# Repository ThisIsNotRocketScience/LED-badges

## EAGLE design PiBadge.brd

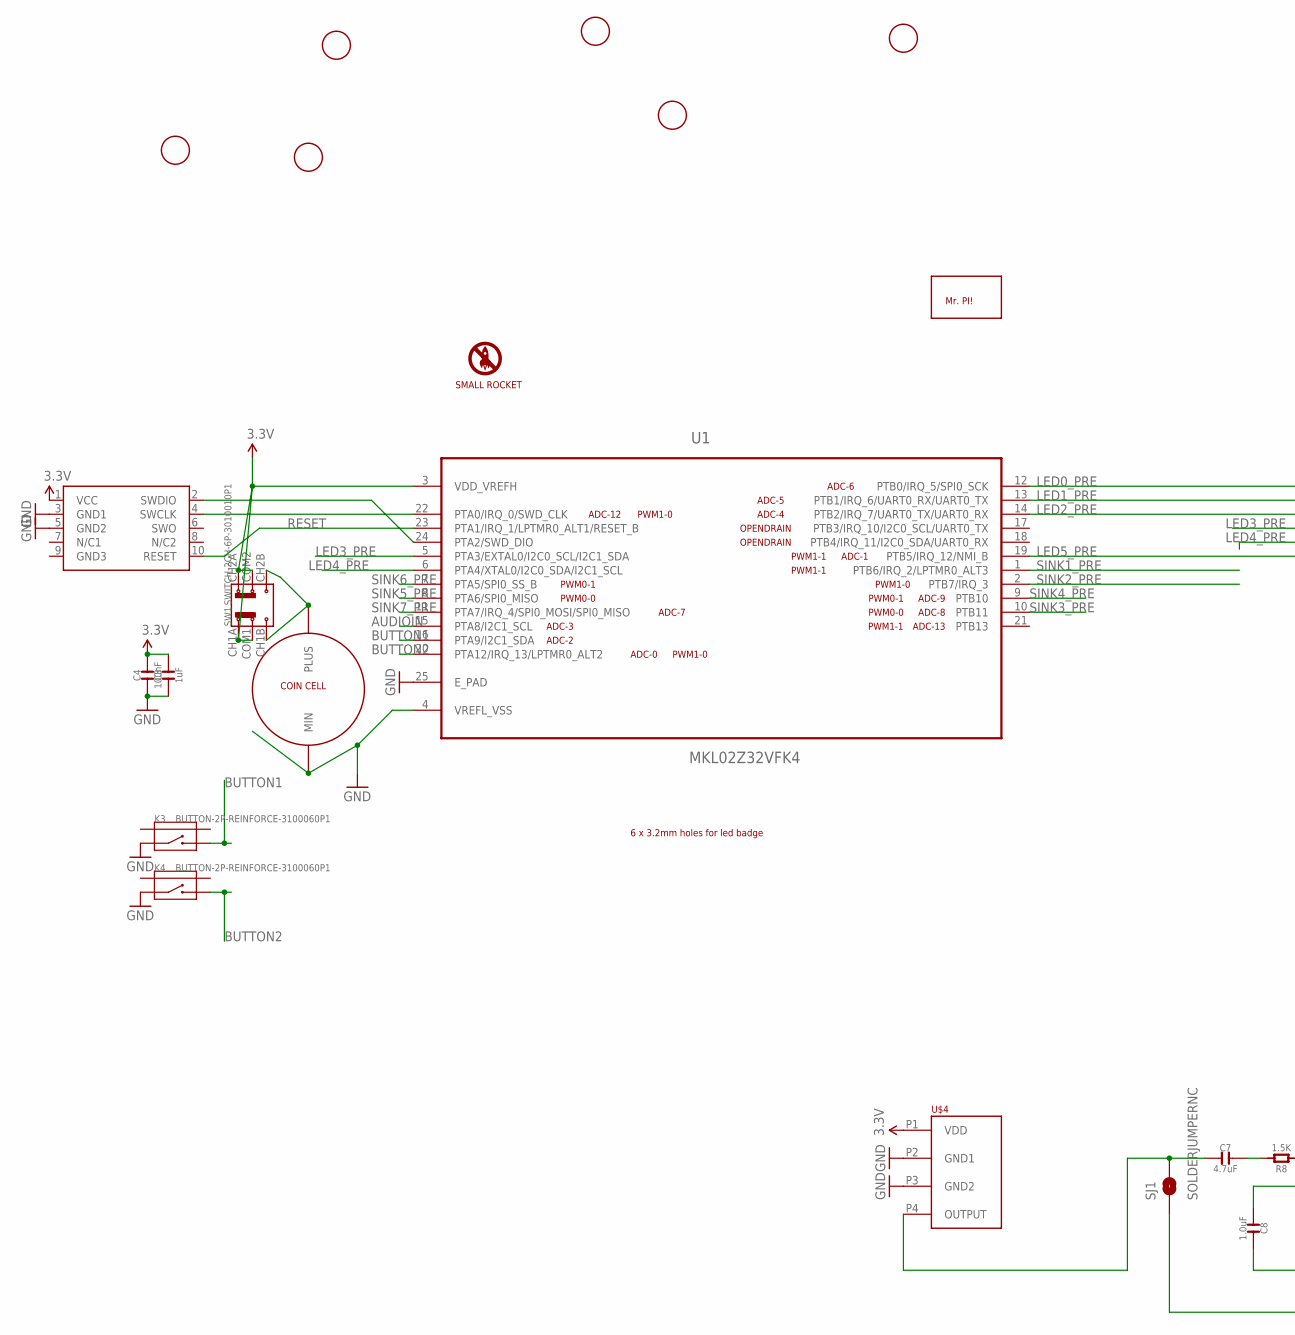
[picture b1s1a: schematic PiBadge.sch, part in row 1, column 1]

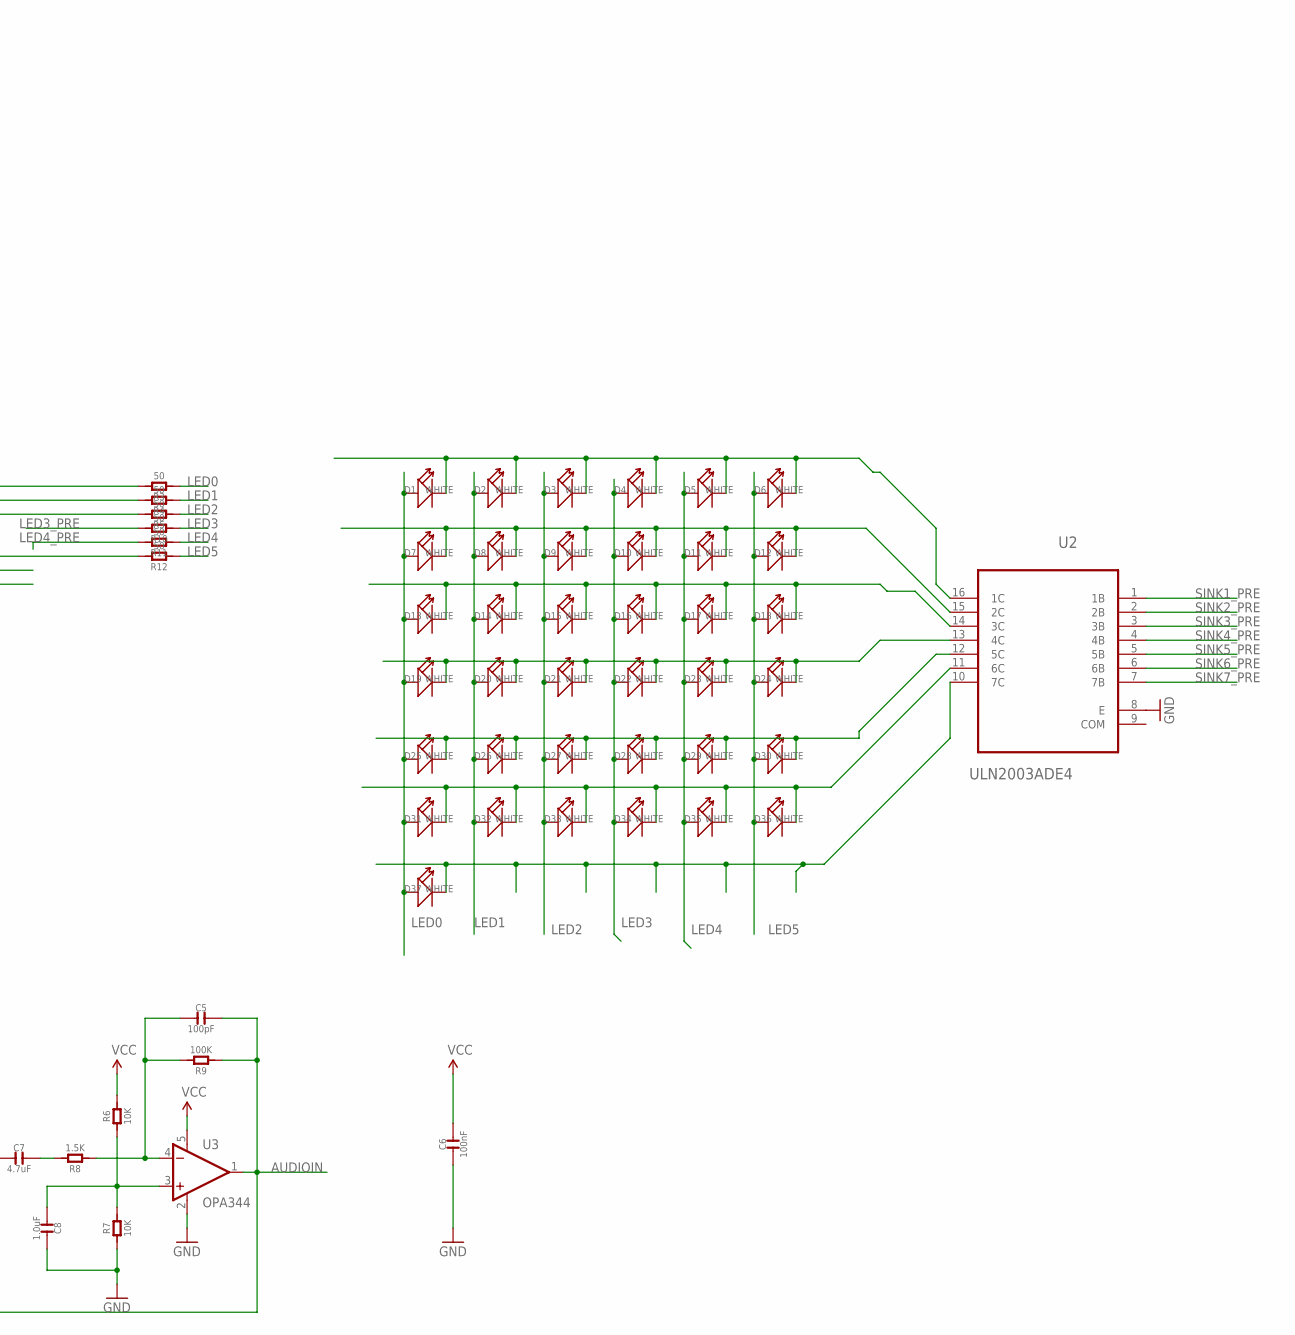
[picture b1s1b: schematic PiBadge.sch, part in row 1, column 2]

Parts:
C3: 1uF; C0603
C4, C6: 100nF; C0603
C5: 100pF; C0603
C7: 4.7uF; C0603
C8: 1.0uF; C0603
D1, D2, D3, D4, D5, D6, D7, D8, D9, D10, D11, D12, D13, D14, D15, D16, D17, D18, D19, D20, D21, D22, D23, D24, D25, D26, D27, D28, D29, D30, D31, D32, D33, D34, D35, D36, D37: WHITE; LED0805
K3, K4: BUTTON-2P-REINFORCE-3100060P1; 4P-SMD-7.0X3.5X3.5H-90D
R3, R4, R5, R10, R11, R12: 50; R0603
R6, R7: 10K; R0603
R8: 1.5K; R0603
R9: 100K; R0603
SJ1: SOLDERJUMPERNC; SJ_2S
SW1: SWITCH-2CH-6P-3010010P1; 6P-2CH-2.54-9.1X3.5X3.2+2H
SWD1: CORTEX_SWD; M50-3600542
U1: MKL02Z32VFK4; QFN50P400X400X100-25N
U2: ULN2003ADE4; SOIC127P600X175-16N
U3: OPA344; SOT23-5
U$1: SMALLROCKET
U$2: COINCELL; 2032HOLDER-SZ
U$3, U$6, U$7, U$8, U$9, U$10: FIDUCIAL; FIDUCIAL_1MM
U$4: WM7120A; LGAMS4
U$5: BADGE_HOLES; BADGEHOLES
U$11: PITINY; TINYPI

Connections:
3.3V: C3.2, C4.2, C6.2, R6.2, SW1.CH1A, SW1.CH2A, SW1.COM1, SW1.COM2, SWD1.1 (VCC), U1.3 (VDD_VREFH), U3.5 (V+), U$4.P1 (VDD)
AUDIOIN: C5.2, R9.1, SJ1.1, U1.15 (PTA8/I2C1_SCL), U3.1 (OUT)
BUTTON1: K3.2, U1.16 (PTA9/I2C1_SDA)
BUTTON2: K4.2, U1.20 (PTA12/IRQ_13/LPTMR0_ALT2)
GND: C3.1, C4.1, C6.1, C8.2, K3.1, K4.1, R7.1, SWD1.3 (GND1), SWD1.5 (GND2), U1.4 (VREFL_VSS), U1.25 (E_PAD), U2.8 (E), U3.2 (V-), U$2.MIN, U$4.P2 (GND1), U$4.P3 (GND2)
LED0: D1.+, D7.+, D13.+, D19.+, D25.+, D31.+, D37.+, R3.1
LED0_PRE: R3.2, U1.12 (PTB0/IRQ_5/SPI0_SCK)
LED1: D2.+, D8.+, D14.+, D20.+, D26.+, D32.+, R4.1
LED1_PRE: R4.2, U1.13 (PTB1/IRQ_6/UART0_RX/UART0_TX)
LED2: D3.+, D9.+, D15.+, D21.+, D27.+, D33.+, R5.1
LED2_PRE: R5.2, U1.14 (PTB2/IRQ_7/UART0_TX/UART0_RX)
LED3: D4.+, D10.+, D16.+, D22.+, D28.+, D34.+, R10.1
LED3_PRE: R10.2, U1.5 (PTA3/EXTAL0/I2C0_SCL/I2C1_SDA)
LED4: D5.+, D11.+, D17.+, D23.+, D29.+, D35.+, R11.1
LED4_PRE: R11.2, U1.6 (PTA4/XTAL0/I2C0_SDA/I2C1_SCL)
LED5: D6.+, D12.+, D18.+, D24.+, D30.+, D36.+, R12.1
LED5_PRE: R12.2, U1.19 (PTB5/IRQ_12/NMI_B)
unnamed: SW1.CH1B, SW1.CH2B, U$2.PLUS
unnamed: SWD1.4 (SWCLK), U1.22 (PTA0/IRQ_0/SWD_CLK)
unnamed: SWD1.2 (SWDIO), U1.24 (PTA2/SWD_DIO)
unnamed: C7.1, SJ1.2, U$4.P4 (OUTPUT)
unnamed: C5.1, R8.1, R9.2, U3.4 (-IN)
unnamed: C7.2, R8.2
unnamed: C8.1, R6.1, R7.2, U3.3 (+IN)
RESET: SWD1.10 (RESET), U1.23 (PTA1/IRQ_1/LPTMR0_ALT1/RESET_B)
SINK1: D1.-, D2.-, D3.-, D4.-, D5.-, D6.-, U2.16 (1C)
SINK1_PRE: U1.1 (PTB6/IRQ_2/LPTMR0_ALT3), U2.1 (1B)
SINK2: D7.-, D8.-, D9.-, D10.-, D11.-, D12.-, U2.15 (2C)
SINK2_PRE: U1.2 (PTB7/IRQ_3), U2.2 (2B)
SINK3: D13.-, D14.-, D15.-, D16.-, D17.-, D18.-, U2.14 (3C)
SINK3_PRE: U1.10 (PTB11), U2.3 (3B)
SINK4: D19.-, D20.-, D21.-, D22.-, D23.-, D24.-, U2.13 (4C)
SINK4_PRE: U1.9 (PTB10), U2.4 (4B)
SINK5: D25.-, D26.-, D27.-, D28.-, D29.-, D30.-, U2.12 (5C)
SINK5_PRE: U1.8 (PTA6/SPI0_MISO), U2.5 (5B)
SINK6: D31.-, D32.-, D33.-, D34.-, D35.-, D36.-, U2.11 (6C)
SINK6_PRE: U1.7 (PTA5/SPI0_SS_B), U2.6 (6B)
SINK7: D37.-, U2.10 (7C)
SINK7_PRE: U1.11 (PTA7/IRQ_4/SPI0_MOSI/SPI0_MISO), U2.7 (7B)

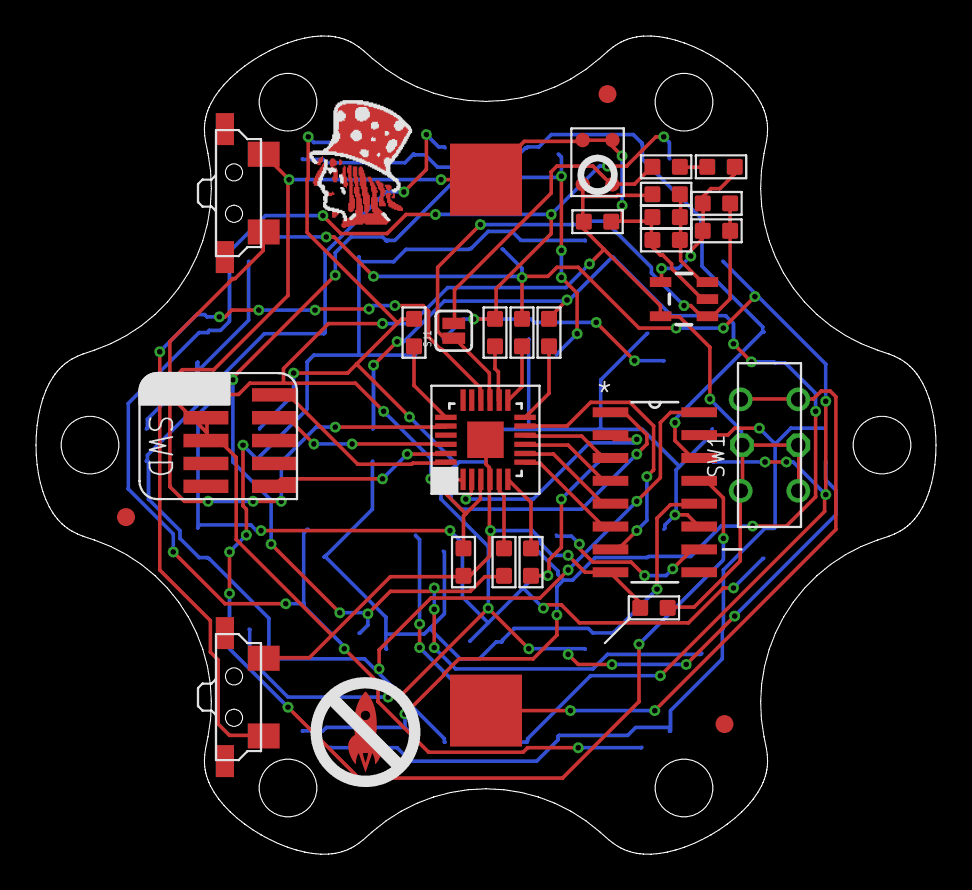
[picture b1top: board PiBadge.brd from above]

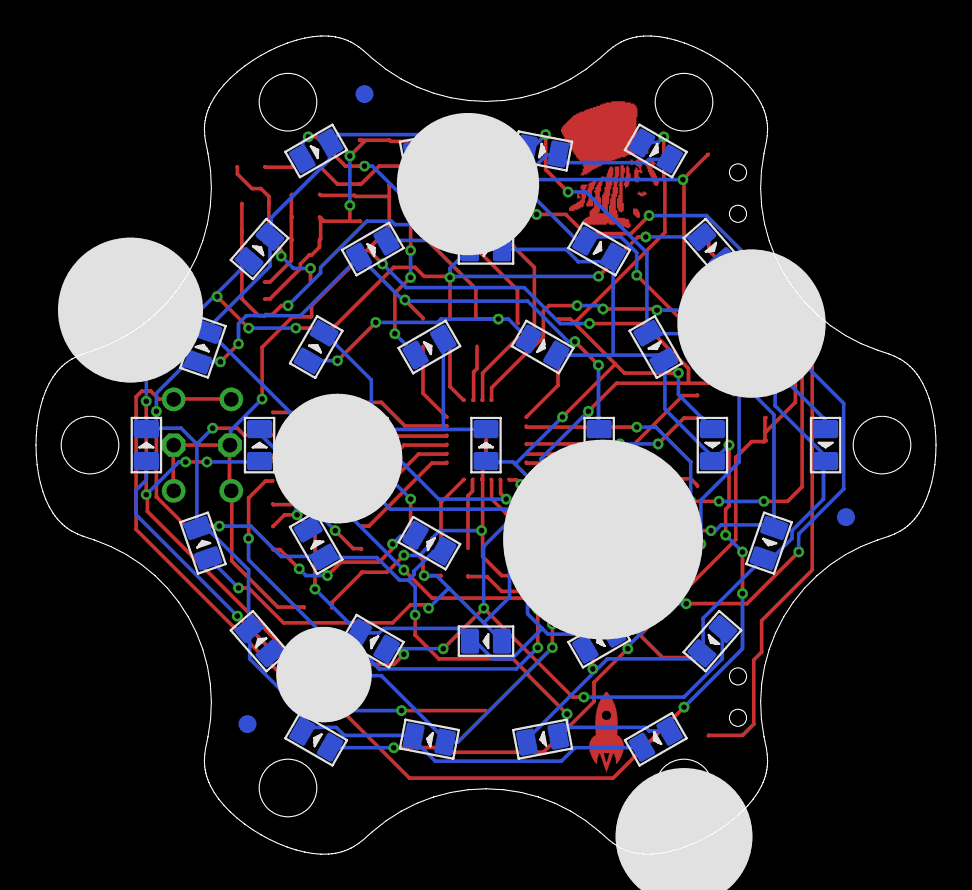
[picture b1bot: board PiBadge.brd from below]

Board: 2 copper layers, 50.0 x 45.5 mm, 72 parts (40 on the bottom side), 39 nets.

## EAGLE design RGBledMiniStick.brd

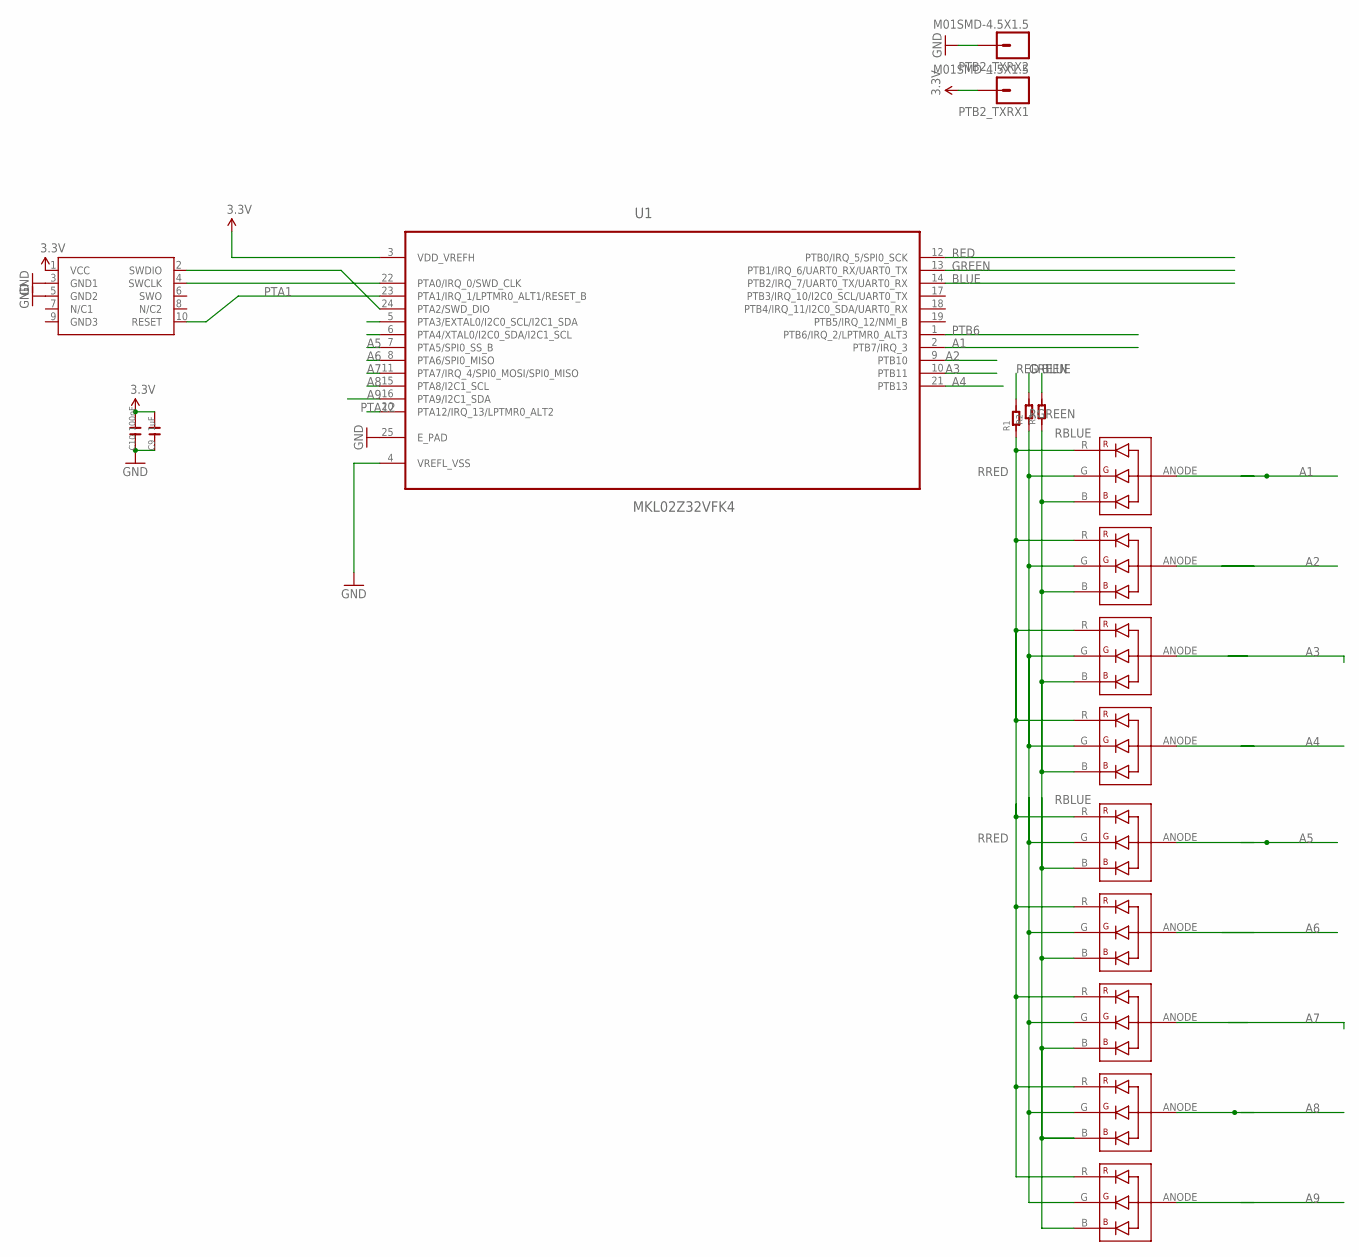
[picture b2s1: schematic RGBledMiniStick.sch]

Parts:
C9: 1uF; C0603
C10: 100nF; C0603
PTB2_TXRX1, PTB2_TXRX2: M01SMD-4.5X1.5; PAD-1.5X4.5
R1, R2, R3: R-0603; R0603
SWD1: CORTEX_SWD; M50-3600542
U1: MKL02Z32VFK4; QFN50P400X400X100-25N
U$1, U$2, U$3, U$4, U$5, U$6, U$7, U$8, U$9: RGBLED_COMMONANODE; 3.5X2.8_RGB_LED

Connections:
3.3V: C9.2, C10.2, PTB2_TXRX1.P$1, SWD1.1 (VCC), U1.3 (VDD_VREFH)
A1: U1.2 (PTB7/IRQ_3), U$1.ANODE
A2: U1.9 (PTB10), U$2.ANODE
A3: U1.10 (PTB11), U$3.ANODE
A4: U1.21 (PTB13), U$4.ANODE
A5: U1.7 (PTA5/SPI0_SS_B), U$5.ANODE
A6: U1.8 (PTA6/SPI0_MISO), U$6.ANODE
A7: U1.11 (PTA7/IRQ_4/SPI0_MOSI/SPI0_MISO), U$7.ANODE
A8: U1.15 (PTA8/I2C1_SCL), U$8.ANODE
A9: U1.16 (PTA9/I2C1_SDA), U$9.ANODE
BLUE: R3.2, U1.14 (PTB2/IRQ_7/UART0_TX/UART0_RX)
GND: C9.1, C10.1, PTB2_TXRX2.P$1, SWD1.3 (GND1), SWD1.5 (GND2), U1.4 (VREFL_VSS), U1.25 (E_PAD)
GREEN: R2.2, U1.13 (PTB1/IRQ_6/UART0_RX/UART0_TX)
unnamed: SWD1.4 (SWCLK), U1.22 (PTA0/IRQ_0/SWD_CLK)
unnamed: SWD1.2 (SWDIO), U1.24 (PTA2/SWD_DIO)
PTA1: SWD1.10 (RESET), U1.23 (PTA1/IRQ_1/LPTMR0_ALT1/RESET_B)
PTA12: U1.20 (PTA12/IRQ_13/LPTMR0_ALT2)
PTB6: U1.1 (PTB6/IRQ_2/LPTMR0_ALT3)
RBLUE: R3.1, U$1.B, U$2.B, U$3.B, U$4.B, U$5.B, U$6.B, U$7.B, U$8.B, U$9.B
RED: R1.2, U1.12 (PTB0/IRQ_5/SPI0_SCK)
RGREEN: R2.1, U$1.G, U$2.G, U$3.G, U$4.G, U$5.G, U$6.G, U$7.G, U$8.G, U$9.G
RRED: R1.1, U$1.R, U$2.R, U$3.R, U$4.R, U$5.R, U$6.R, U$7.R, U$8.R, U$9.R

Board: 2 copper layers, 19 parts (5 on the bottom side), 20 nets, no tracks yet.

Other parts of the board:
U$10: SMALLROCKET-SILKONLY

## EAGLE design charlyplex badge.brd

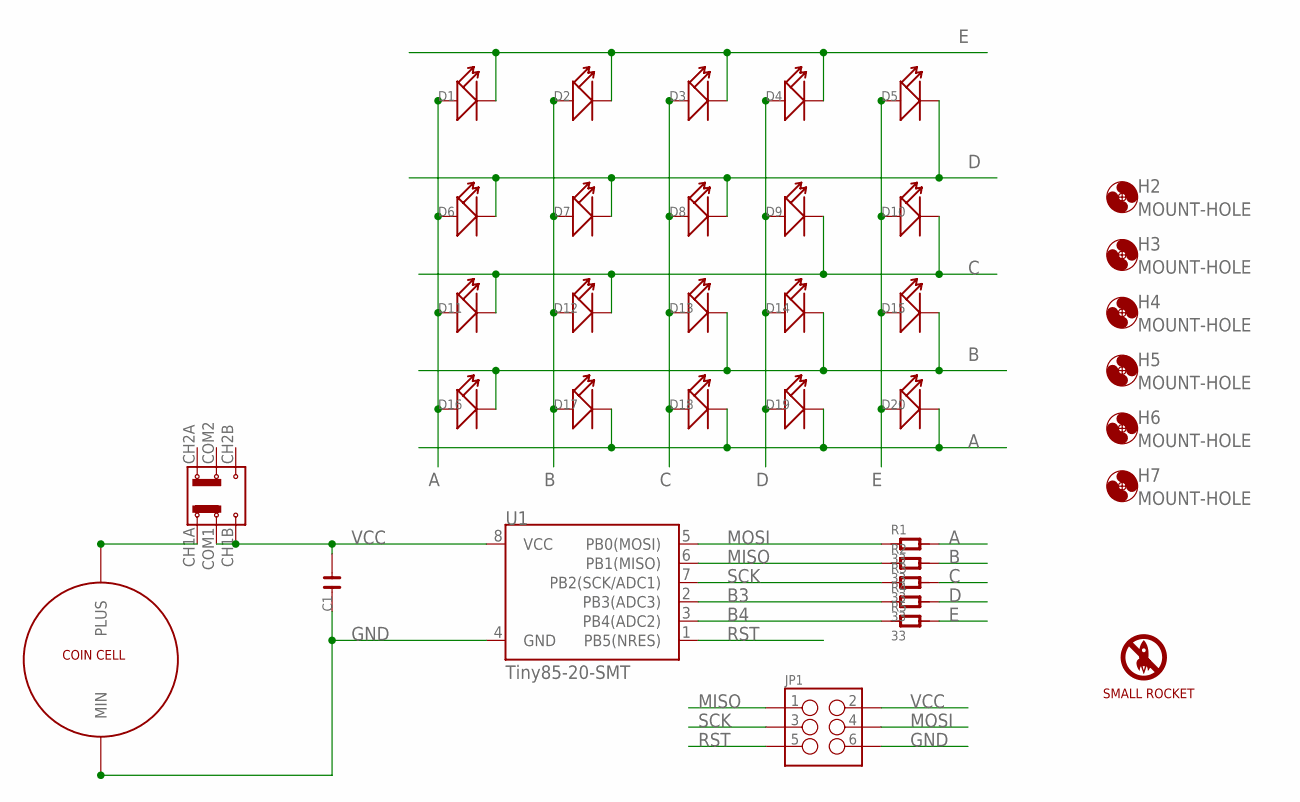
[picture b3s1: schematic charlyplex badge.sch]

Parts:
C1: C-0603; C0603
D1, D2, D3, D4, D5, D6, D7, D8, D9, D10, D11, D12, D13, D14, D15, D16, D17, D18, D19, D20: LED; LED0603
H2, H3, H4, H5, H6, H7: MOUNT-HOLE; 3.2-NOMARKINGS-SMALLSAFEZONE
JP1: M03X2SMT; 2X3_SMT_POSTS
R1, R2, R3, R4, R5: 33; R0603
SW1: SWITCH-2CH-6P-3010010P1; 6P-2CH-2.54-9.1X3.5X3.2+2H
U1: Tiny85-20-SMT; SO08-EIAJ
U$1: COINCELL; 2032HOLDER-SZ
U$2: SMALLROCKET

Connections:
A: D1.+, D6.+, D11.+, D16.+, D17.-, D18.-, D19.-, D20.-, R1.2
B: D2.+, D7.+, D12.+, D13.-, D14.-, D15.-, D16.-, D17.+, R2.2
B3: R4.1, U1.2 (PB3(ADC3))
B4: R5.1, U1.3 (PB4(ADC2))
C: D3.+, D8.+, D9.-, D10.-, D11.-, D12.-, D13.+, D18.+, R3.2
D: D4.+, D5.-, D6.-, D7.-, D8.-, D9.+, D14.+, D19.+, R4.2
E: D1.-, D2.-, D3.-, D4.-, D5.+, D10.+, D15.+, D20.+, R5.2
GND: C1.1, JP1.6, U1.4 (GND), U$1.MIN
MISO: JP1.1, R2.1, U1.6 (PB1(MISO))
MOSI: JP1.4, R1.1, U1.5 (PB0(MOSI))
unnamed: SW1.CH1A, U$1.PLUS
RST: JP1.5, U1.1 (PB5(NRES))
SCK: JP1.3, R3.1, U1.7 (PB2(SCK/ADC1))
VCC: C1.2, JP1.2, SW1.CH1B, SW1.COM1, U1.8 (VCC)

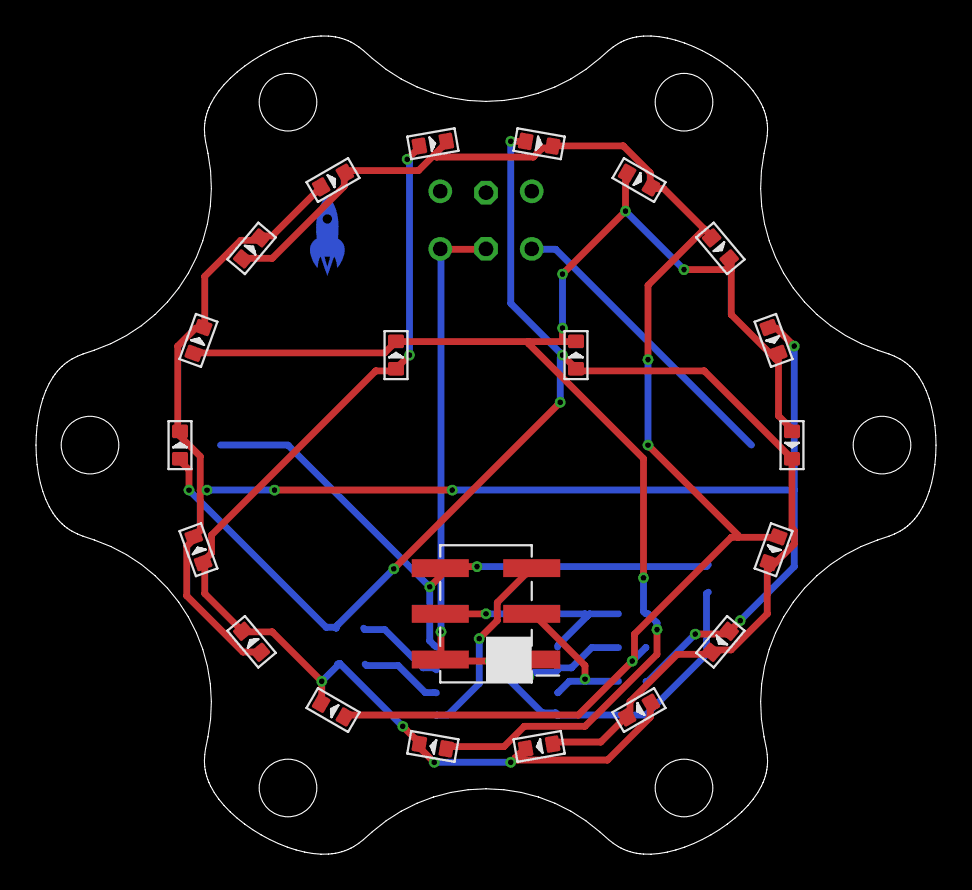
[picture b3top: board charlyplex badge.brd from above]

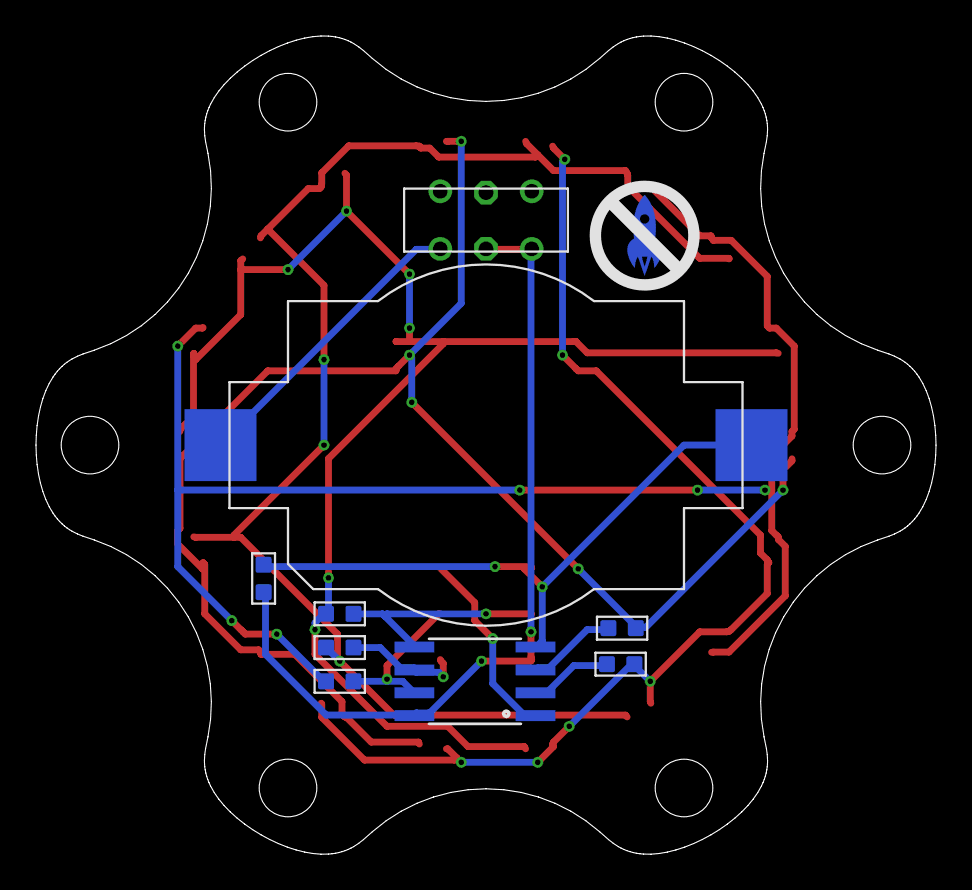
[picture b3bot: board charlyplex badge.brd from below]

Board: 2 copper layers, 50.0 x 45.5 mm, 37 parts (10 on the bottom side), 14 nets.

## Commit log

2016-02-16 :circus_tent: Added .gitattributes & .gitignore files
2016-02-16 Led badge initial commit - this is the one that went to BoomFestival 2014
2016-10-10 Added mr. Pi
2016-10-10 NewBadges
2016-10-11 PiBadge
2016-10-11 PiTrance

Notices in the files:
parts and their libraries:
SparkFun-Passives: Licensing: CC v3.0 Share-Alike You are welcome to use this library for commercial purposes.
